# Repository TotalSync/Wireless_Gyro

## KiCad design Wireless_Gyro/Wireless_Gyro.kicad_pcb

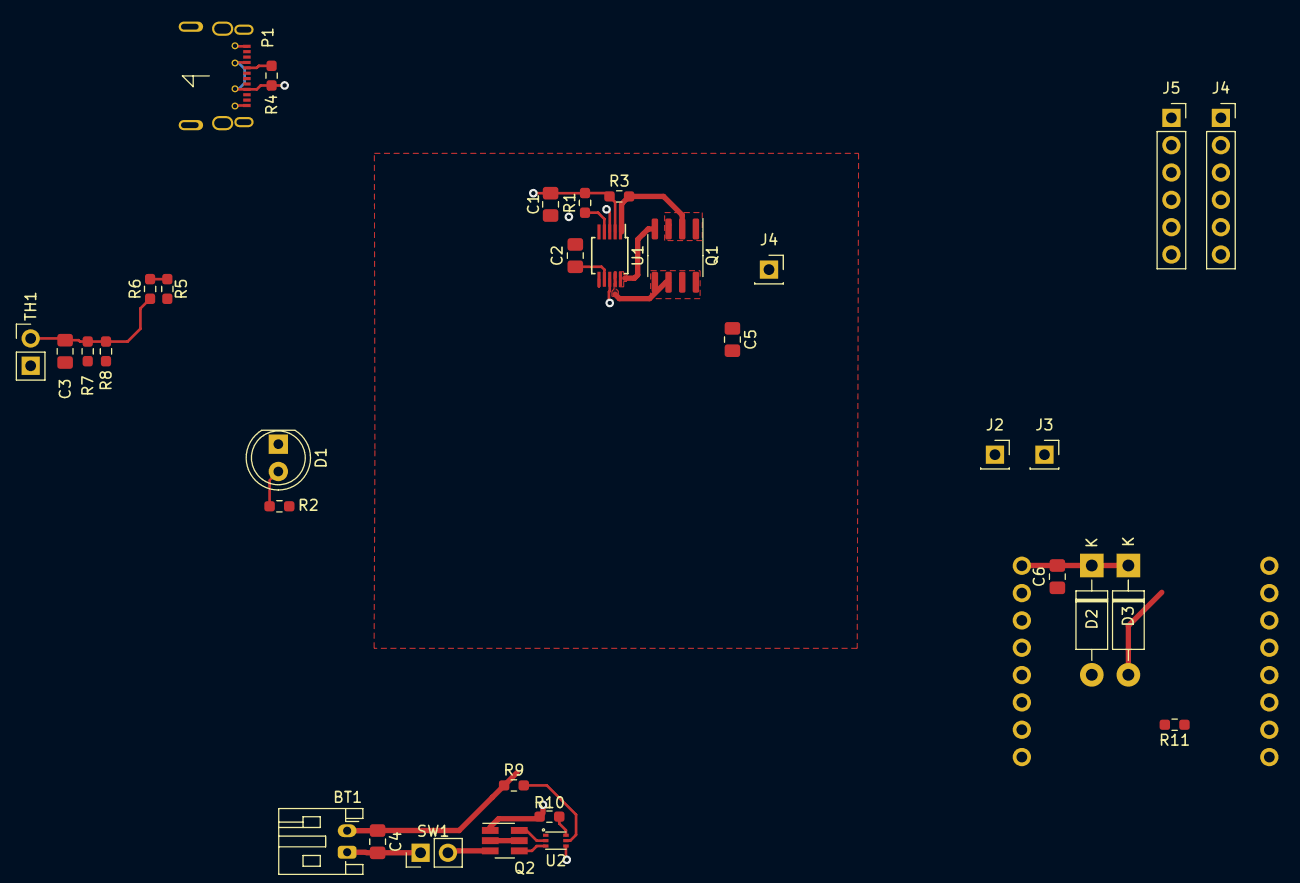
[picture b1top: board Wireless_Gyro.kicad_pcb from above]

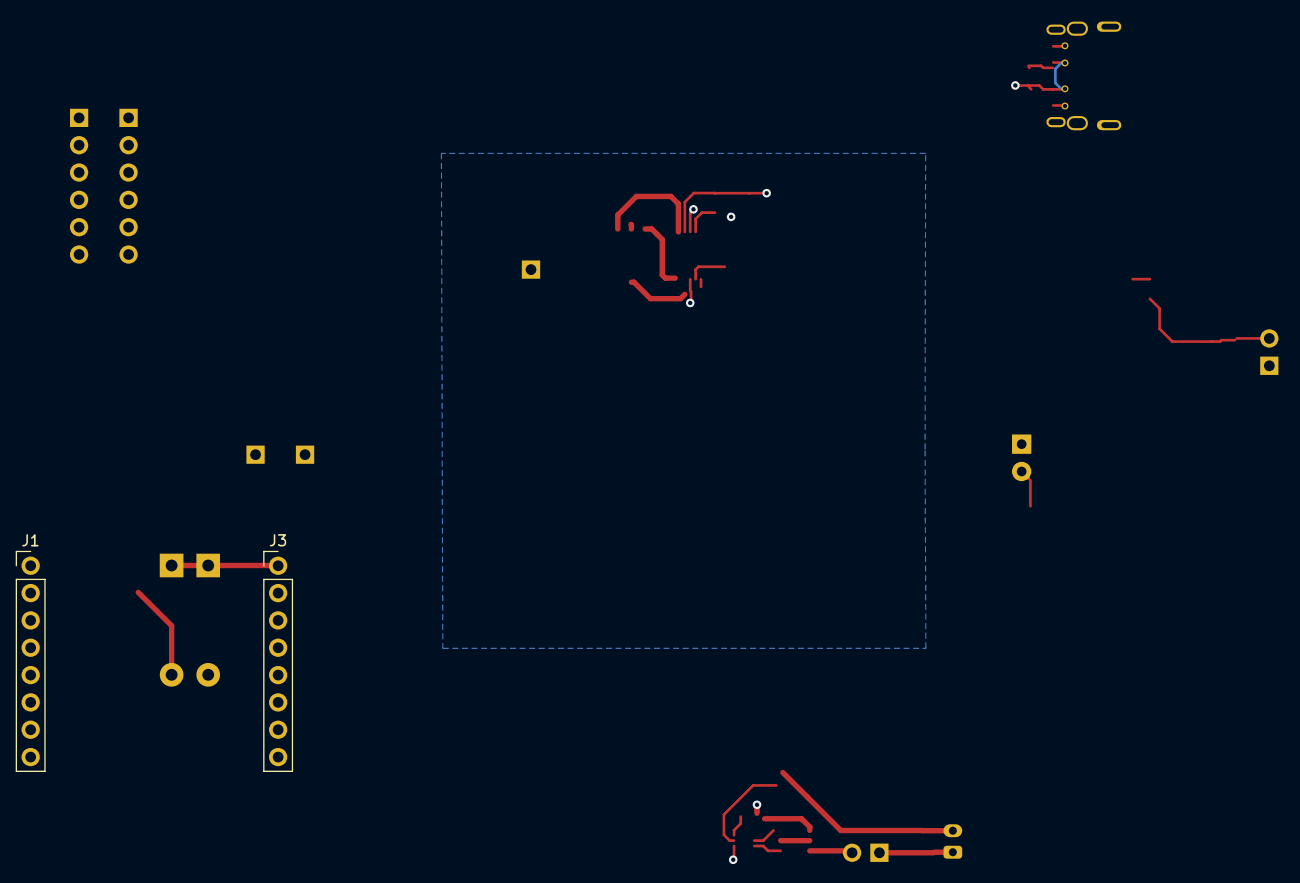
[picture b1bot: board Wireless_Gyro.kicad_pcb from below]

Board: 4 copper layers, 35 parts (2 on the bottom side), 25 nets.

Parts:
BT1: Battery_Cell; JST_PH_S2B-PH-K_1x02_P2.00mm_Horizontal
C1, C4, C5, C6: 10uF; C_0805_2012Metric_Pad1.18x1.45mm_HandSolder
C2: 100nF; C_0805_2012Metric_Pad1.18x1.45mm_HandSolder
C3: 1nF; C_0805_2012Metric_Pad1.18x1.45mm_HandSolder
D1: Green; LED_D5.0mm_Clear
D2, D3: 1N5817; D_DO-41_SOD81_P10.16mm_Horizontal
J1, J3#2: Conn_01x08_Female; PinHeader_1x08_P2.54mm_Vertical
J2: Gyro GND; PinSocket_1x01_P2.54mm_Vertical
J3: INT-D5; PinSocket_1x01_P2.54mm_Vertical
J4: 3.3V; PinSocket_1x01_P2.54mm_Vertical
J4#2, J5: Conn_01x06_Female; PinSocket_1x06_P2.54mm_Vertical
P1: USB_C_Plug_USB2.0; USB_C_THT
Q1: IRF7404; SOIC-8_3.9x4.9mm_P1.27mm
Q2: Q_Dual_NMOS_S1G1D2S2G2D1; SOT-23-6_Handsoldering
R1, R2: 1k; R_0603_1608Metric_Pad0.98x0.95mm_HandSolder
R3: 150m; R_0603_1608Metric_Pad0.98x0.95mm_HandSolder
R4, R5: 22k; R_0603_1608Metric_Pad0.98x0.95mm_HandSolder
R6, R8: 10k; R_0603_1608Metric_Pad0.98x0.95mm_HandSolder
R7: 100k; R_0603_1608Metric_Pad0.98x0.95mm_HandSolder
R9: 330; R_0603_1608Metric_Pad0.98x0.95mm_HandSolder
R10: 470; R_0603_1608Metric_Pad0.98x0.95mm_HandSolder
R11: 220k; R_0603_1608Metric_Pad0.98x0.95mm_HandSolder
SW1: SW_SPDT; PinHeader_1x02_P2.54mm_Vertical
TH1: 10k; PinHeader_1x02_P2.54mm_Vertical
U1: MCP73841; MSOP-10_3x3mm_P0.5mm
U2: S-8240AAW-I6T1U; SNT-6A

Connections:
+3.3V: C5.1, J1.1, J4.1, J4#2.2
+5V: C1.1, D2.2 (A), P1.A4 (VBUS), P1.A9 (VBUS), P1.B4 (VBUS), P1.B9 (VBUS), R1.2, R2.2, R3.1, R4.1, U1.2 (V_{DD})
/INT: J1.5, J4#2.6
/SCL: J3#2.6, J4#2.4
/SDA: J3#2.5, J4#2.5
GND: BT1.2 (-), C1.2, C2.1, C3.2, C4.2, J4#2.3, P1.A1 (GND), P1.A12 (GND), P1.B1 (GND), P1.B12 (GND), R7.2, R8.2, SW1.1 (A), TH1.2, U1.8 (V_{SS}), U2.4 (VSS)
Load: C6.1, D2.1 (K), D3.1 (K), J3#2.1
unnamed: BT1.1 (+), C4.1, D3.2 (A), Q1.5 (D), Q1.6 (D), Q1.7 (D), Q1.8 (D), R9.1, R11.2, U1.9 (V_{BAT})
unnamed: C2.2, U1.7 (TIMER)
unnamed: C3.1, R5.2, R6.2, R7.1, R8.1, TH1.1, U1.6 (TH_{ERM})
unnamed: C5.2, C6.2, J2.1, J3#2.2, Q2.1 (S), R10.2
unnamed: D1.1 (K), U1.3 (STAT1)
unnamed: D1.2 (A), R2.1
unnamed: J1.7, R11.1
unnamed: P1.A5 (CC), R4.2
unnamed: Q1.1 (S), Q1.2 (S), Q1.3 (S), R3.2, U1.1 (SENSE)
unnamed: Q1.4 (G), U1.10 (DRV)
unnamed: Q2.2 (D), Q2.5 (D)
unnamed: Q2.3 (S), SW1.2 (B)
unnamed: Q2.4 (G), U2.3 (DO)
unnamed: Q2.6 (G), U2.2 (CO)
unnamed: R1.1, U1.4 (EN)
unnamed: R5.1, R6.1, U1.5 (TH_{REF})
unnamed: R9.2, U2.5 (VDD)
unnamed: R10.1, U2.6 (VM)

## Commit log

2023-03-30 Uploading Local changes to fix remote tracking
